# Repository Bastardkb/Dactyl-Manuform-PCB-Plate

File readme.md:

# Dactyl Manuform Mini PCB - plate

Flexible PCB made for the Dactyl Manuform Mini - up to 6x6 and breakable down to 5x3.

This repository contains all files necessary to order a PCB.

If you want to modify the design files, the Kicad sources are included (you will need a 5.99 nightly version).
If you just want to order the PCBs, check out the Release section which contain the gerber files.

## How to order

Order with a 0.6mm PCB thickness

## License

Licensed under CC BY-NC-SA 4.0
Copyright Quentin Lebastard 2021

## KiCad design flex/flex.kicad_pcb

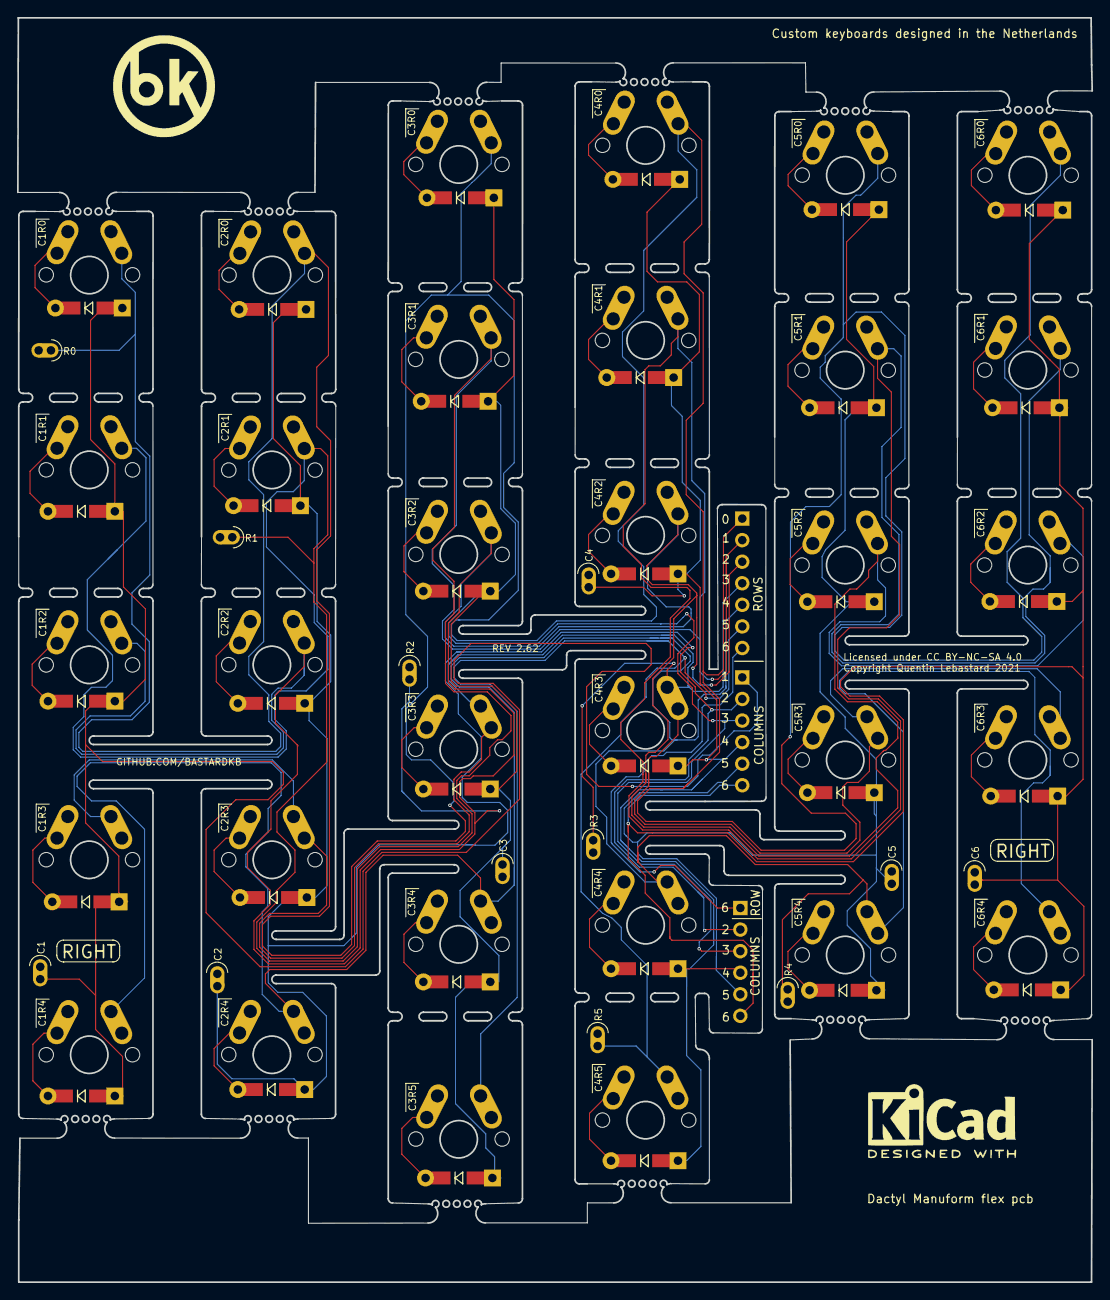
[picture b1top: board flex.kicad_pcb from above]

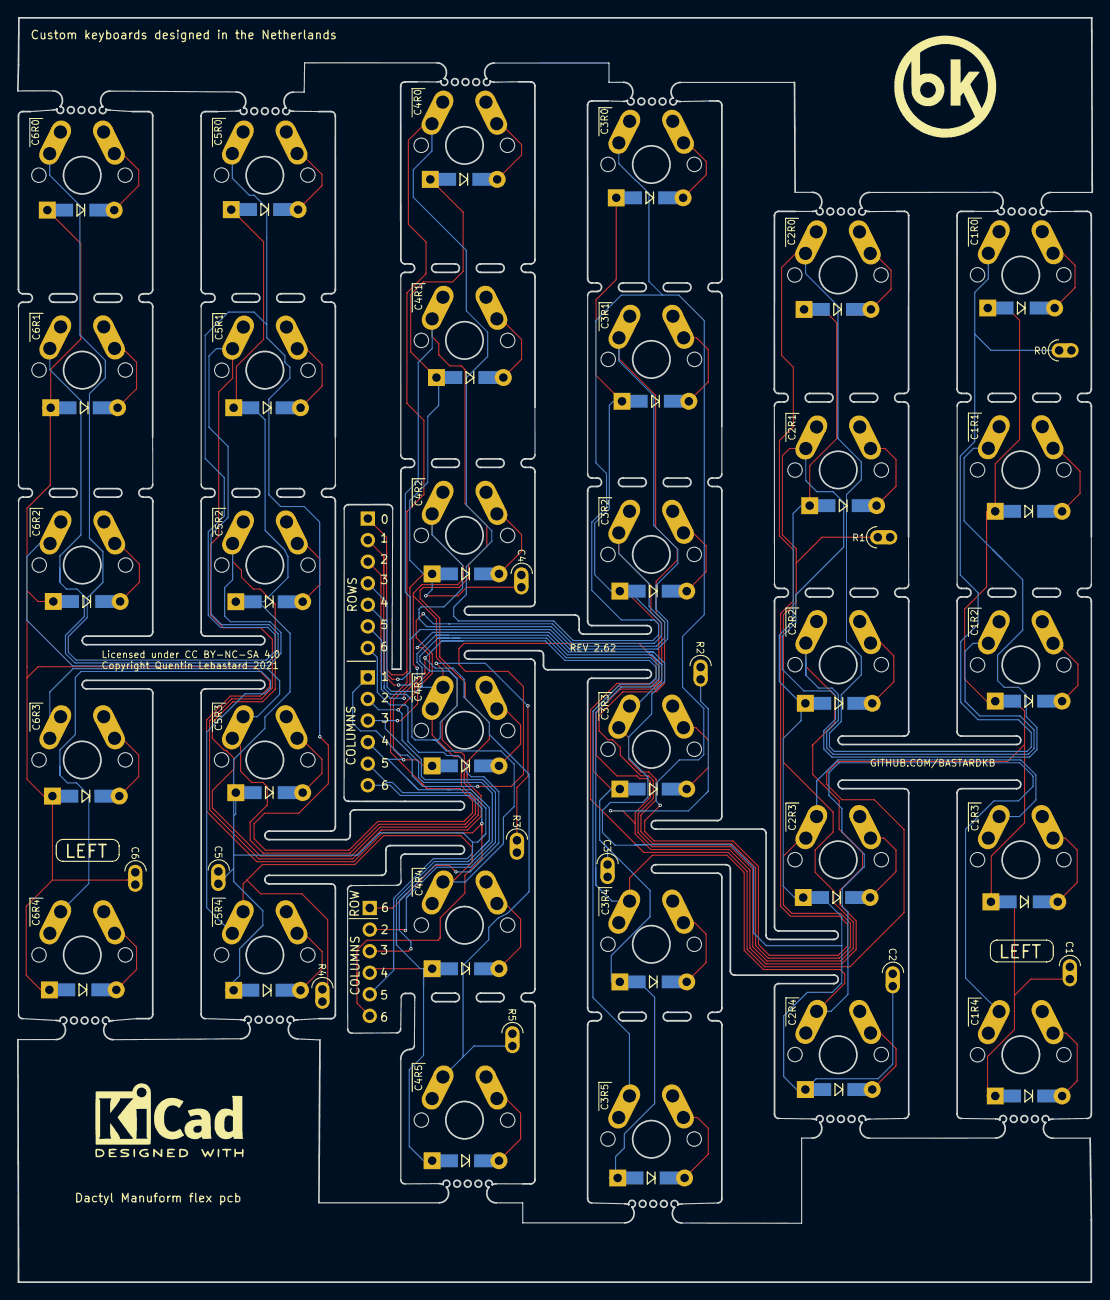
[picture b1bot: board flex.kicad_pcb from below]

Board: 2 copper layers, 126.5 x 148.9 mm, 79 parts (58 on the bottom side), 45 nets.

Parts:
D1, D2, D3, D4, D5, D6, D7, D8, D9, D10, D11, D12, D13, D14, D15, D16, D17, D18, D19, D20, D21, D22, D23, D24, D25, D26, D27, D28, D29, D30, D31, D32: D; Diode_TH_SOD123
J1, J14: Conn_01x06_Female; PinSocket_1x06_P2.54mm_Vertical
J2: Conn_01x07_Female; PinSocket_1x07_P2.54mm_Vertical
J3, J4, J5, J6, J7, J8, J9, J10, J11, J12, J13, J15: Conn_01x02_Female; SolderWire-0.15sqmm_1x01_D0.5mm_OD1.5mm
SW1, SW2, SW3, SW4, SW5, SW6, SW7, SW8, SW9, SW10, SW11, SW12, SW13, SW14, SW15, SW16, SW17, SW18, SW19, SW20, SW21, SW22, SW23, SW24, SW25, SW26, SW27, SW28, SW29, SW30, SW31, SW32: SW_Push; SW_MX_reversible

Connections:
unnamed: D1.2 (A), SW1.2
unnamed: D2.2 (A), SW2.2
unnamed: D3.2 (A), SW3.2
unnamed: D4.2 (A), SW4.2
unnamed: D5.2 (A), SW5.2
unnamed: D6.2 (A), SW6.2
unnamed: D7.2 (A), SW7.2
unnamed: D8.2 (A), SW8.2
unnamed: D9.2 (A), SW9.2
unnamed: D10.2 (A), SW10.2
unnamed: D11.2 (A), SW11.2
unnamed: D12.2 (A), SW12.2
unnamed: D13.2 (A), SW13.2
unnamed: D14.2 (A), SW14.2
unnamed: D15.2 (A), SW15.2
unnamed: D16.2 (A), SW16.2
unnamed: D17.2 (A), SW17.2
unnamed: D18.2 (A), SW18.2
unnamed: D19.2 (A), SW19.2
unnamed: D20.2 (A), SW20.2
unnamed: D21.2 (A), SW21.2
unnamed: D22.2 (A), SW22.2
unnamed: D23.2 (A), SW23.2
unnamed: D24.2 (A), SW24.2
unnamed: D25.2 (A), SW25.2
unnamed: D26.2 (A), SW26.2
unnamed: D27.2 (A), SW27.2
unnamed: D28.2 (A), SW28.2
unnamed: D29.2 (A), SW29.2
unnamed: D30.2 (A), SW30.2
unnamed: D31.2 (A), SW31.2
unnamed: D32.2 (A), SW32.2
col1: D1.1 (K), D2.1 (K), D3.1 (K), D4.1 (K), D27.1 (K), J9.1, J14.1
col2: D5.1 (K), D6.1 (K), D7.1 (K), D8.1 (K), D28.1 (K), J1.2, J10.1, J14.2
col3: D9.1 (K), D10.1 (K), D11.1 (K), D12.1 (K), D13.1 (K), D29.1 (K), J1.3, J11.1, J14.3
col4: D14.1 (K), D15.1 (K), D16.1 (K), D17.1 (K), D18.1 (K), D30.1 (K), J1.4, J12.1, J14.4
col5: D19.1 (K), D20.1 (K), D21.1 (K), D22.1 (K), D31.1 (K), J1.5, J13.1, J14.5
col6: D23.1 (K), D24.1 (K), D25.1 (K), D26.1 (K), D32.1 (K), J1.6, J14.6, J15.1
row0: J2.1, J3.1, SW27.1, SW28.1, SW29.1, SW30.1, SW31.1, SW32.1
row1: J2.2, J4.1, SW1.1, SW5.1, SW9.1, SW14.1, SW19.1, SW23.1
row2: J2.3, J5.1, SW2.1, SW6.1, SW10.1, SW15.1, SW20.1, SW24.1
row3: J2.4, J6.1, SW3.1, SW7.1, SW11.1, SW16.1, SW21.1, SW25.1
row4: J2.5, J7.1, SW4.1, SW8.1, SW12.1, SW17.1, SW22.1, SW26.1
row5: J2.6, J8.1, SW13.1, SW18.1
row6: J1.1, J2.7

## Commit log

2021-09-20 add files
